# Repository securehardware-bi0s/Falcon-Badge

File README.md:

# Falcon-Badge

**Work in progress.**
**Check the OTA branch**

## Layout
```
├── bin
│   ├── falcon-fire.bin
│   ├── final-unlocked.bin
│   ├── game_of_life.bin
│   ├── initial.bin
│   └── serial-exploitation.bin
├── hw
│   ├── Assembly
│   ├── DrillFiles
│   ├── GerberFiles
│   ├── InCTF_Badge.brd
│   └── InCTF_Badge.sch
├── LICENSE
├── README.md
└── src
    ├── falcon-fire
    ├── Final
    ├── Game-Of-Life
    ├── initial
    │   ├── data
    └── serial-exploitation
```
### Software Pre-requisities
Software to install:
* For Windows:
    * [USB-UART Driver](https://www.silabs.com/products/development-tools/software/usb-to-uart-bridge-vcp-drivers)
* On Linux/Windows:
    * pyserial -> ```pip install pyserial```
    * esptool -> ```pip install esptool```
        * For more info visit [esptool](https://github.com/espressif/esptool).
    * miniterm.py (Installed with pyserial)

### Binaries

* falcon-fire.bin
    * A version of the 80s *Asteroid* Game.
* final-unlocked.bin
    * Firmware with unlocked LEDs and defence against laser attacks.
* game_of_life.bin
    * A version of *Conway's Game of Life* on Falcon.
* initial.bin
    * The basic firmware everyone's badge was loaded with.
* serial-exploitation.bin
    * Firmware that was designed to teach you serial exploitation.

### How to flash the firmware?

Make sure you've installed the correct drivers and the ```esptool.py```
Clone the repository and open a terminal in the same directory.
Run the following command with the desired file in the same terminal.
```
esptool.py write_flash 0x00000 initial.bin
```
### Source Code
The code is written with the help of [Arduino](https://github.com/esp8266/Arduino) SDK, considering it to be beginner-friendly platform. You can run [MicroPython](https://docs.micropython.org/en/latest/esp8266/tutorial/intro.html) on the same board as well.
#### The structure
The badge has the personal data of the users stored in the SPIFFS system. Hence we use the 4MB flash memory in NodeMCU with 1MB specified for filesystem.
If you're interested in learning more about the [Filesystem](https://arduino-esp8266.readthedocs.io/en/latest/filesystem.html) used in ESP8266 Arduino. 
This filesystem consists of the following files:
```
data/
├── chall.png -> The forensics challenge desgined by @_f41c0n
├── flag -> For the game 
├── id -> Cadet/Padawan/Rebel ID
├── ip -> Static IP Assigned to each badge
├── name -> Username
├── pass -> 5 char of username and 5 char of the phone number

```
#### Some of the used libraries include
* [ThingPulse SSD1306](https://github.com/ThingPulse/esp8266-oled-ssd1306)
* [Adafruit GFX](https://github.com/adafruit/Adafruit-GFX-Library)
* [Adafruit SSD1306](https://github.com/adafruit/Adafruit_SSD1306)
* [u8g2](https://github.com/olikraus/u8g2)
* Already included in the base installation
    * Wire
    * FS
#### How to compile? 
* If you have successfully installed Arduino IDE , you can just clone the code to get started.

You might face an issue of creating a new folder, just press "OK" and continue.
* If you like the makefile approach then I suggest you look at [makeEspArduino](https://github.com/plerup/makeEspArduino) project.
    * To build 
        ```make -f makeEspArduino.mk all FLASH_DEF=4M1M```
    * For flashing the code 
        ```make -f makeEspArduino.mk flash FLASH_DEF=4M1M```
    * For flashing the filesystem 
        ```make -f makeEspArduino.mk flash_fs FLASH_DEF=4M1M```
        
### Write-Ups 
<h3>You sure?</h3><details>

## Web Challenge
`?id=100` gives the correct flag

## Image Challenge
There is a base64 text appended to the image. Extracting and decoding it will give a table of 8 columns representing the 8 bits of each character.
Extract the binary data and decode it to get the flag.

## Serial Exploitation
The challenge starts with a login screen and on choosing the login option requires you to enter a randomly generated OTP. On analysis we can see that the LDR which is connected to the analog pin of the NodeMCU is used as the random seed for generating pseudo-random values. 

If we short the analog pin with the VCC the random seed value will remain constant and so the pattern of generated OTP will remain constant. So by using a sample code to generate the OTP pattern or by brute-force you can login to the system.

Once you login, you will get an option to read data from the board. You only have permission to read a maximum of 50 characters. But the array from which you are reading data is a byte array of size 260. The input given is to a signed 8 bit variable and the program first checks if the value is greater less than 50. After the initial condition is passed the value is moved to an unsigned 8 bit variable and then that many number of characters from the array is printed. So if we enter a negative number like ‘-1’ it will bypass the initial check and when the value is moved to the unsigned variable -1 becomes 255 and we can read 255 characters from the array. The flag is stored from the 188th index so the output we get by giving -1 as the input will contain the flag!

FLAG : falcon{y0u_3xtr4ct3d_th3_s3ctr3t_d4t4}
</details>

### To-Do

* [x] Add Source Code
* [x] Add OTA and MQTT Code (Check the OTA branch)
* [x] Add Write-Ups

### Credits

GameOfLife based on: [DrMikeG](https://raw.githubusercontent.com/DrMikeG/Conway/master/GameOfLife/GameOfLife.ino)

Falcon-Fire based on: [pauls-3d-things](https://github.com/pauls-3d-things/arduino-space-hopper)

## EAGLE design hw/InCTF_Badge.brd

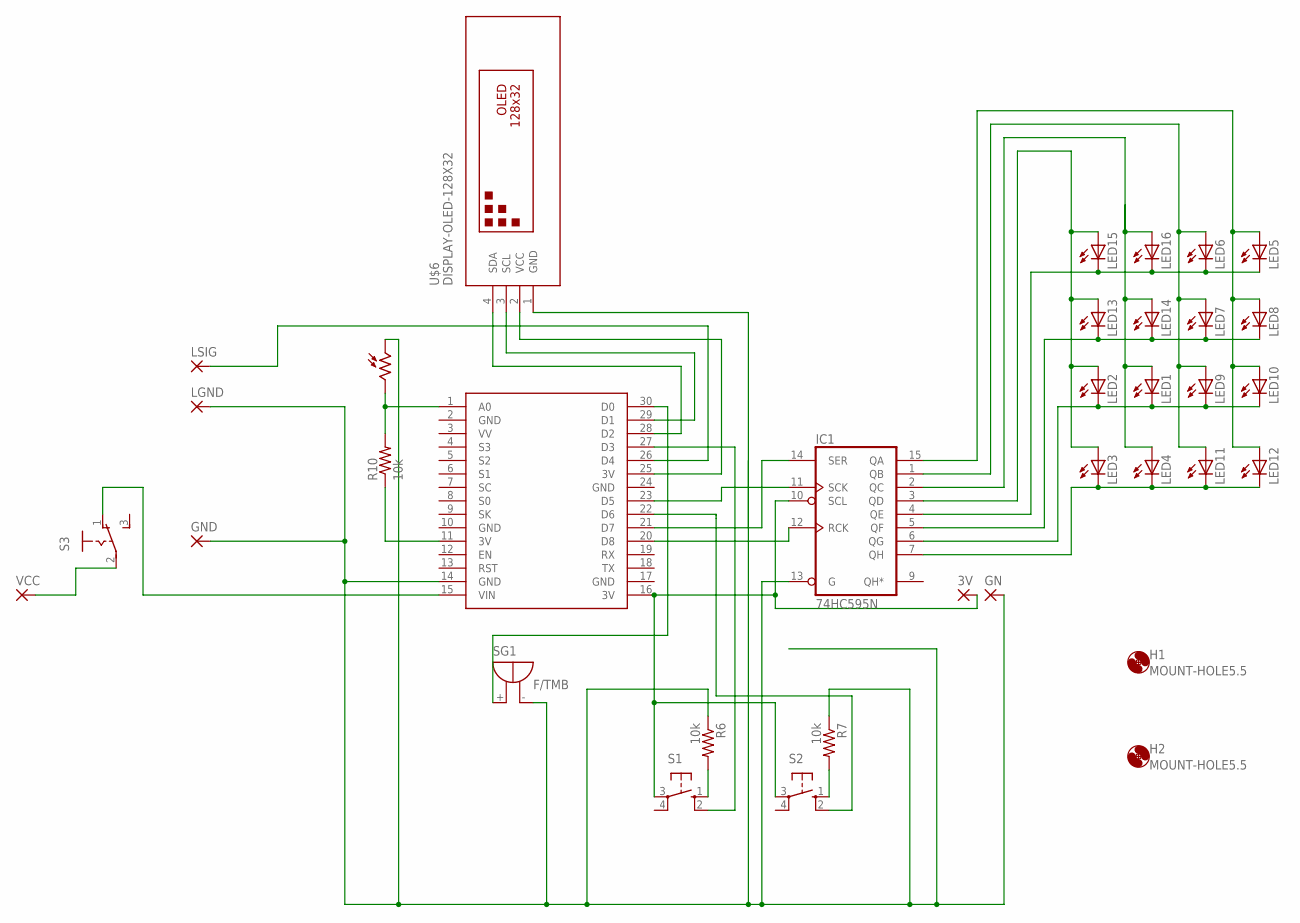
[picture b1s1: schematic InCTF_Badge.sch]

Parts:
3V: 1,6/0,8
GN: 1,6/0,8
GND: 1,6/0,8
H1, H2: MOUNT-HOLE5.5; 5,5
IC1: 74HC595N; DIL16
LED1, LED2, LED3, LED4, LED5, LED6, LED7, LED8, LED9, LED10, LED11, LED12, LED13, LED14, LED15, LED16: LED5MM
LGND: 1,6/0,8
LSIG: 1,6/0,8
PH1: A1050_09; T0-46-A10XX
R6, R7, R10: 10k; 0204/5
S1, S2: 10-XX; B3F-10XX
S3: 255SB
SG1: F/TMB
U$1: NODEMCU
U$6: DISPLAY-OLED-128X32
VCC: 1,6/0,8

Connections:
GND: U$1.10 (GND), U$1.17 (GND), U$1.24 (GND)
unnamed: IC1.14 (SER), U$1.21 (D7)
unnamed: U$1.29 (D1), U$6.3 (SCL)
unnamed: U$1.28 (D2), U$6.4 (SDA)
unnamed: U$1.25 (3V), U$6.2 (VCC)
unnamed: IC1.12 (RCK), U$1.20 (D8)
unnamed: IC1.11 (SCK), U$1.23 (D5)
unnamed: S3.1 (O), U$1.15 (VIN)
unnamed: S1.2 (S1), U$1.27 (D3)
unnamed: LSIG.1, U$1.26 (D4)
unnamed: IC1.4 (QE), LED5.K (C), LED6.K (C), LED15.K (C), LED16.K (C)
unnamed: IC1.5 (QF), LED7.K (C), LED8.K (C), LED13.K (C), LED14.K (C)
unnamed: IC1.6 (QG), LED1.K (C), LED2.K (C), LED9.K (C), LED10.K (C)
unnamed: IC1.7 (QH), LED3.K (C), LED4.K (C), LED11.K (C), LED12.K (C)
unnamed: S3.2, VCC.1
unnamed: R10.1, U$1.11 (3V)
unnamed: SG1.+, U$1.30 (D0)
unnamed: IC1.3 (QD), LED2.A, LED3.A, LED13.A, LED15.A
unnamed: IC1.2 (QC), LED1.A, LED4.A, LED14.A, LED16.A
unnamed: IC1.1 (QB), LED6.A, LED7.A, LED9.A, LED11.A
unnamed: IC1.15 (QA), LED5.A, LED8.A, LED10.A, LED12.A
unnamed: 3V.1, IC1.10 (SCL), S1.3, S2.3, U$1.16 (3V)
unnamed: R6.2, S1.1 (S)
unnamed: R7.2, S2.1 (S)
unnamed: PH1.2, R10.2, U$1.1 (A0)
unnamed: IC1.8 (GND), U$1.2 (GND)
S2: S2.2 (S1), U$1.22 (D6)
V: GN.1, GND.1, IC1.13 (G), LGND.1, PH1.1, R6.1, R7.1, SG1.-, U$1.14 (GND), U$6.1 (GND)
VCC: IC1.16 (VCC)

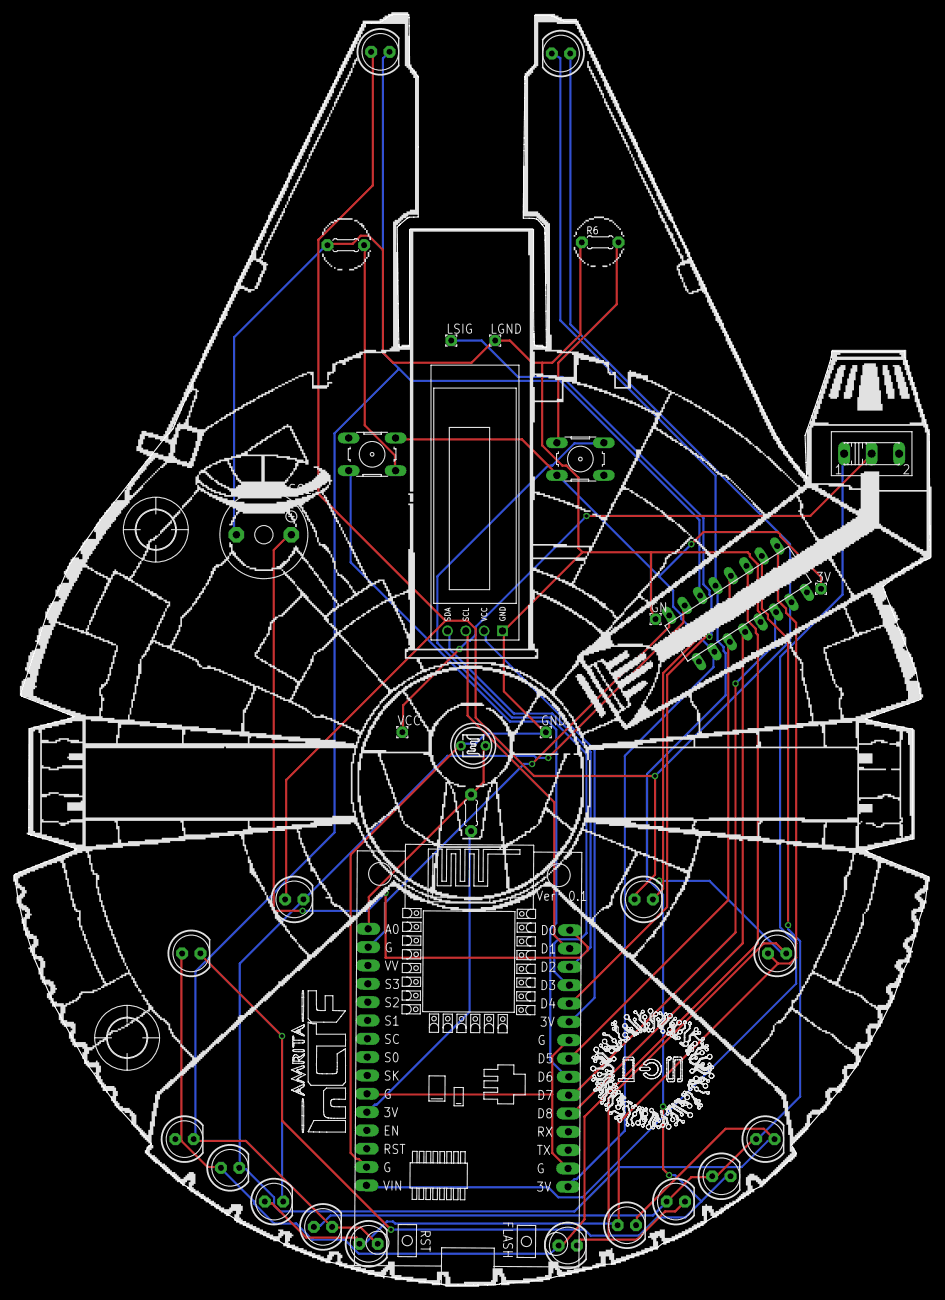
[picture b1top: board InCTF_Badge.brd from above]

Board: 2 copper layers, 126.9 x 176.2 mm, 35 parts (0 on the bottom side), 28 nets.

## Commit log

2020-01-03 First CMT
2020-01-03 Adding bins
2020-01-06 Added Code
2020-01-08 Error Fix
2020-01-11 Adding HW Design Files
2020-03-10 OTA Updates
2020-05-18 OTA: Add support for server.client()
2020-05-18 src: Add OTA/MQTT firmware
    Added original firmware used for the badge
2020-05-18 README: Update the README to reflect new branch
    Update info about hardware and OTA branch
2020-05-24 README: Update short write-ups

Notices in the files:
parts and their libraries:
oled: Released under the Creative Commons Attribution 4.0 International License: http://creativecommons.org/licenses/by/4.0
